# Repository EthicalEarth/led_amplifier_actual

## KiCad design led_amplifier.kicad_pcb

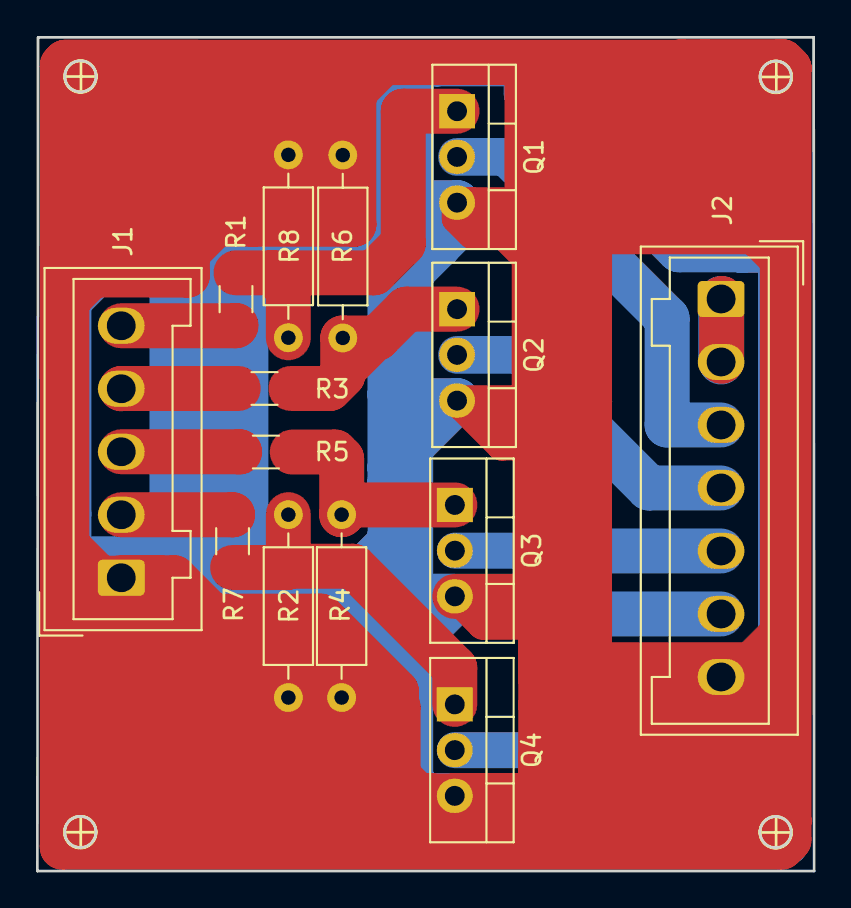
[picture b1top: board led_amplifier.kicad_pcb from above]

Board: 2 copper layers, 43.2 x 46.3 mm, 14 parts (0 on the bottom side), 14 nets.

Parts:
J1: Conn_01x05; Wago_734-135_1x05_P3.50mm_Vertical
J2: Conn_01x07_Female; Wago_734-137_1x07_P3.50mm_Vertical
Q1, Q2, Q3, Q4: IRF3205; TO-220-3_Vertical
R1, R3, R5, R7: R; R_1206_3216Metric
R2, R4, R6, R8: R; R_Axial_DIN0207_L6.3mm_D2.5mm_P10.16mm_Horizontal

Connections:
unnamed: J1.1, J2.7, Q1.3, Q2.3, Q3.3, Q4.3, R2.2, R4.2, R6.2, R8.2
unnamed: J1.2, R7.2
unnamed: J1.3, R5.2
unnamed: J1.4, R3.2
unnamed: J1.5, R1.2
unnamed: J2.1, J2.2
unnamed: J2.3, Q1.2
unnamed: J2.4, Q2.2
unnamed: J2.5, Q3.2
unnamed: J2.6, Q4.2
unnamed: Q1.1, R1.1, R8.1
unnamed: Q2.1, R3.1, R6.1
unnamed: Q3.1, R4.1, R5.1
unnamed: Q4.1, R2.1, R7.1

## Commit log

2021-08-25 Update...
